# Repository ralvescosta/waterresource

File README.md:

# Water Resource

<br />
<br />

<p align="justify">
Water Resource é um projeto open source que tem como intuito apresentar para a comunidade de desenvolvimento um sistema de automação residencial utilizando o conceito de internet das coisas, integrando tecnologias modernas como: NodeJs, WebSocket, ReactJs, ESP32 dentre outras. O objetivo da aplicação é apresentar uma forma de monitorar e controlar o nível de um reservatório de água, juntamente com uma interface ao usuário, onde o usuário poderá acompanhar em tempo real o estado do sistema e interagir com o sensor configurando alguns parâmetros de aquisição. O sistema foi projetado para fornecer ao usuário confiabilidade e facilidade de controle. Leia mais sobre a aplicação em:
</p>

> https://waterresource.hopto.org

## Get Started

<p align="justify">
A seguir tem-se os passos para poder replicar os recursos do projeto, os itens Servidor-Local e Servidor-Remoto precisam ser hospedados em um ambiente virtual que tenha suporte para o mesmo, no minimo 1GB de memória RAM e 25GB de armazenamento. Cada tópico apresenta as medidas necessárias para poder colocar a aplicação em funcionamento tanto em um servidor local quanto em um servidor remoto.
</p>

- [Firmware](#Firmware)
  - [Premissas](##Premissas)
  - [Bibliotecas](##Bibliotecas)
  - [Upload-do-Firmware](##Embarcar-Firmware)
- [Servidor-Local](#Servidor-Local)
  - [Premissas](##Premissas)
  - [Back-End](##Back-End)
  - [Front-End](##Front-End)
- [Servidor-Remoto](#Servidor-Remoto)
  - [Premissas](##Premissas)
  - [Back-End](##Back-End)
  - [Front-End](##Front-End)
- [Hardware](#Hardware)
- [Referências](#Referências)
- [Licença](#Licença)

## Firmware

### Premissas

Inicialmente deve-se instalar o compilador utilizado:

- <a href="https://www.arduino.cc/en/Main/Software" target="_blank">Arduino IDE</a>

<p align="justify">
Com a IDE do Arduino devidamente instalada, instale as dependências da placa do ESP32 para que seja possível embarcar o firmewere no devKit ESP32, seguindo este <a href="https://www.fernandok.com/2018/09/instalando-esp32-no-arduino-ide-metodo.html" target="_blank">tutorial</a>.
</p>

<p align="justify">
Atente-se para o fato, que o projeto foi baseado na arquitetura do ESP32, sendo assim o funcionamento do mesmo só é garantido utilizando-o.
</p>

Após realizar devidamente as instalações clone o repositório:

> git clone https://github.com/rafaelbodao/waterresource.git

### Bibliotecas

<p align="justify">
Com a IDE devidamente configurada agora faz-se necessário instalar as bibliotecas que foram utilizadas no projeto. Por meio do gerenciador de bibliotecas da IDE, faça o download da biblioteca WiFi na versão 1.27 e ArduinoJson na versão 6.9.1. Ainda na instalação das bibliotecas porém agora instalando por meio de arquivos .zip, faça o download do seguintes repositórios com o formato .zip e insira-os na IDE <a href="https://github.com/zhouhan0126/WIFIMANAGER-ESP32" target="_blank">repositório 1</a>, <a href="https://github.com/zhouhan0126/DNSServer---esp32" target="_blank">repositório 2</a> e <a href="https://github.com/zhouhan0126/WebServer-esp32" target="_blank">repositório 3</a>
</p>

<p align="justify">
A biblioteca Web Service instalada por meio do repositório 3, possui um erro em sua arquitetura que faz gerar um conflito na renderização de um elemento HTML, assim faz-se necessário alterar o nome deste elemento no arquivo HTTP_Method.h. Para acessar este arquivo, só é possível por meio  do terminal. Com o Git Bash aberto deve-se acessar o diretório da biblioteca por meio do comando:
</p>

> cd c:\Users\YOUR_USER\AppData\Local\Arduino15\packages\esp32\hardware\esp32\1.0.0\libraries\WebService

<p align="justify">
Atente-se onde está escrito YOUR_USER deve-se inserir o usuário do computador onde foi instalado todas as dependências anteriormente. Ao acessar o devido diretório execute:
</p>

> sudo nano HTTP_Method.h

<p align="justify">
Acessando assim o conteúdo do arquivo. Encontre:
</p>

> HTTP_HEAD = 0b00100000

<p align="justify">
e substitua por:
</p>

> HTTP_HEADER = 0b00100000.

<p align="justify">
Após utilize o comando para fechar e salvar as alterações:
</p>

> Control + X

### Upload-do-Firmware
<p align="justify">
Com o repositório devidamente clonado, acesse o diretório firmware/WaterResource, abra e compile o arquivo WaterResource.ino. Após a compilação, faça o upload do firmware. A figura abaixo apresenta o esquemático a ser seguido para instalar os periféricos.
</p>

<p align="justify">
O protótipo desenvolvido com base no DevKit ESP32 e alguns outros periféricos tem como intuito ser uma plataforma de testes e não um produto para possível produção. O desenvolvimento de um hardware para a produção deve ser baseado no microcontrolador <a href="https://www.espressif.com/sites/default/files/documentation/esp32_datasheet_en.pdf" target="_blank">MCU ESP32</a> e não no DevKit ESP32, assim alem de reduzir consideravelmente o custo de cada sensor, o desepenho e a durabilidade do micocontrolador sera bem maior pois o mesmo tera apenas as funcionalidades necessarias para aplicação.
</p>

## Servidor-Local

### Premissas

Inicialmente instale os seguintes itens abaixo:

- <a href="https://nodejs.org/en/" target="_blank">NodeJs</a>
- <a href="https://gitforwindows.org/" target="_blank">Git Bash</a>
- <a href="https://www.apachefriends.org/pt_br/index.html" target="_blank">XAMPP</a>

Instale o gerenciador de processos <a href="http://pm2.keymetrics.io/" target="_blank">PM2</a>:

> sudo npm install pm2 -g

*Se estiver utilizando o Windows faz-se necessário executar o terminal como administrador

### Back-End

<p align="justify">
Com o repositório Water Resource clonado, e todos os passos anteriores realizados, acesse o diretório do repositório por meio do terminal, dentro da pasta backEnd execute o seguinte comando:
</p>

> npm install

<p align="justify">
Ao executá-lo será instalado todas as dependências necessárias. Na pasta backEnd, existe um arquivo denominado .env.exemple, porém este arquivo só pode ser visualizado por meio do terminal ou por algum editor de texto como por exemplo VSCode, ainda na pasta backEnd execute os comandos abaixo sequencialmente:
</p>

> cp .env.exemple .env

> sudo nano .env

<p align="justify">
Abrindo o conteúdo do arquivo, este arquivo contém as variáveis de ambiente que configuram toda a aplicação de back-end, caso você tenha seguido os passos anterior devidamente, simplesmente delete todo o conteúdo e copie o conteúdo logo abaixo e cole dentro do arquivo, caso tenha realizado os procedimentos anteriores de outra forma, entre com as devidas informações conforme é solicitado.
</p>

```javascript
module.exports = {
username: "root",
password: "",
database: "test",
host: "127.0.0.1",
dialect: "mysql",
saltRounds: 10,
tokenKey: "WR_2019_LOCAL_SERVER",
gmail:'YOUR_EMAIL_TO_SEND@gamil.com',
emailPassword: 'YOUR_EMAIL_PASSWORD',
}
```

<p align="justify">
Note que os campos gmail e emailPassword, deve ser inserido um e-mail e senha do gmail utilizado para enviar o email de confirmação de cadastro. Para que a aplicação de confirmação de cadastro por e-mail possa funcionar corretamente é necessário habilitar o acesso de aplicações de terceiros no gmail, faça o logIn no e-mail que deseja configurar e acesse este <a href="https://myaccount.google.com/lesssecureapps?utm_source=google-account&utm_medium=web" target="_blank">link</a>, habilitando assim o acesso a terceiros. Em seguida inicie o servidor Apache e o infraestrutura de banco de dados MySQL provida pelo XAMPP.
</p>

No diretório do backEnd digite o seguinte comando:

> node_modules\.bin\sequelize db:migrate

<p align="justify">
Ao executar este comando, se realizado os passos anteriores corretamente, será criado no banco de dados local a estrutura de persistência de dados, esta estrutura pode ser verificada acessando a aplicação de gerenciamento de banco de dados phpMyAdmin, digite em seu navegador de internet:
</p>

> localhost/phpmyadmin

<p align="justify">
Dentro da interface acesse o banco de dados test. A figura abaixo apresenta como é disposta a estrutura de dados.
</p>

<p align="justify">
O último passo é executar o servidor, para isso ainda dentro do diretório backEnd execute o seguinte comando:
</p>

> pm2 start src/server.js

<p align="justify">
Neste momento o servidor que cuidará de todas requisições provenientes do gateway (ESP 32) e da interface do usuário já está devidamente funcionando. Caso deseje verificar os status do servidor, basta digitar o seguinte comando:
</p>

> pm2 list

<p align="justify">
Caso queira parar o servidor, utilize o seguinte comando:
</p>

> pm2 stop src/server.js

### Front-End

<p align="justify">
Após realizar o procedimentos do Back-End em servidor local, abra uma nova aba do terminal e acesse o diretório frontEnd, execute o seguinte comando:
</p>

> npm install

<p align="justify">
Da mesma forma que foi realizado anteriormente, faz-se necessário modificar o arquivo de variáveis ambientes para configurar a aplicação, acesse o diretório frontEnd/src, por meio do comando:
<p>

> cd frontEnd/src

<p align="justify">
Altere o nome do arquivo “environment.exemple.js” para “environment.js”, utilizando o seguinte comando:
<p>

> mv environment.exemple.js environment.js

<p align="justify">
Se todos os passos foram seguidos corretamente, a única alteração necessária no arquivo será inserir o Ip local de onde a aplicação está sendo provida, assumindo o Ip local sendo: 192.168.100.3 a arquivo de configuração ficará:
<p>

```javascript
import socket from "socket.io-client"

/*
 * Dashboard exports
 */
export const dashboadURL = "http://192.168.100.3:3000";

export const socketIO = socket("http://192.168.100.3:3333");

export const difereceTime = 2;
/*
 * SignUp exports 
 */
export const hrefURL = "http://192.168.100.3:3000";

/*
 * Services exports
 */

//API AXIOS SERVICES
export const serverBaseURL = "http://192.168.100.3:3333";

//TOKEN ID
export const TOKEN_ID = "WR_IFMG"

```

<p align="justify">
Porém se foi realizado algum procedimento diferente, altere o arquivo environment.js conforme a necessidade. Por fim execute os comando abaixo em sequência:
</p>

> npm run build

> pm2 start server.js

<p align="justify">
Assim a aplicação Web estará pronta para uso em sua rede local, a mesma pode ser acessada por outros dispositivos que estiverem conectados a sua rede, basta acessar o Ip do computador que estiver hospedando a aplicação como por exemplo: 192.168.100.3:3000
</p>

<p align="justify">
Observação 1: Para que o serviço Web seja acessado é necessário realizar todos os procedimentos de inicialização, desde inicialização do XAMPP até a inicialização do Front-End.
</p>

<p align="justify">
Observação 2: O gateway está configurado para enviar as aquisições para o servidor local considerando um userId = 1, sendo assim faz necessário alterar o endereço do servidor local nas variáveis globais dentro do firmware e o Id do usuário criado no ato do cadastro do mesmo, considerando que o endereço Ip local do servidor seja 192.198.100.3 e o Id do usuario seja 1, a configuração das variáveis pode ser feita:
</p>

> \#define urlConfiguration “http://192.168.100.3:3333/gateway/configuration”

> \#define urlComunication “http://192.168.100.3:3333/gatewat/nivel”

> \#define userId 1

<!--  -->
## Servidor-Remoto

### Premissas

<p align="justify">
Para realizar o procedimento aqui apresentado faz-se necessário ter acesso a uma máquina virtual hospedada em alguma empresa de hospedagem. Utilizou-se uma máquina virtual hospedada no servidor da <a href="https://www.apachefriends.org/pt_br/index.html" target="_blank">Digital Ocean</a>, tendo 1GB de memória RAM, 25GB de armazenamento, com o sistema operacional Ubuntu 16.04.5 x64. Os procedimentos aqui apresentados funcionam especificamente para o sistema operacional utilizado.
</p>

<p align="justify">
Além da infraestrutura de hospedagem, faz-se necessário criar um “Sistema de nome de domínio” (DNS) para poder apontar para o Ip de sua máquina virtual, existem diversos provedores de DNS gratuitos, para a execução deste utilizou-se o <a href="https://www.apachefriends.org/pt_br/index.html" target="_blank">NO-IP</a>.
</p>

<p align="justify">
Após a criação do droplet Digital Ocean, será informado um acesso remoto a máquina virtual. Este acesso é criado de forma automática, com um usuário Root e uma senha. Existem boas práticas para poder configurar a conexão ssh com a máquina virtual, porém fica a cargo do leitor as realizá-las, neste iremos utilizar o acesso da forma em que é fornecido.
</p>

<p align="justify">
Antes de realizar o procedimento de hospedagem em um servidor remoto, realize o procedimento para servidor local, pois alguns passos realizados anteriormente serão fundamentais para esta etapa.
</p>

<p align="justify">
Abra o terminal de sua máquina local utilizando o Git Bash e digite os comandos sequencialmente:
</p>

> sudo apt-get updtae

> sudo apt-get install ssh

<p align="justify">
Tendo criado devidamente o droplet, o acesso a máquina virtual será realizado via conexão ssh por meio do IPv4 fornecido, considerando que o IPv4 fornecido seja “000:000:000:000”, execute o comando abaixo:
</p>

> ssh root@000:000:000:000

<p align="justify">
Em seguida será solicitado a senha de acesso, inserido a senha fornecida, você realizará o acesso remoto a seu ambiente de produção. Inicialmente faz-se necessário realizar a instalação de três dependências persistentes no pacote LEMP e configurá-las devidamente. A sigla LEMP representa as arquiteturas de desenvolvimento L = Linux, E = Enginex (nginx), M = MySQL e P = PHP, por meio destes pacotes podemos configurar toda a infraestrutura que vai receber a aplicação web.</p>

##### MySQL Server

<p align="justify">
A tecnologia MySQL é um ambeinte de desenvolvimento complexo e robusto, na sua versão 5.7 utiliza a base dados do MariaDB, execute o comando abaixo:
</p>

> sudo apt-get install mysql-server

<p align="justify">
Após a finalização da instalação do servidor MySQL, faz-se necessário configurá-lo, para isso digite o comando abaixo:
</p>

> mysql_secure_installation

<p align="justify">
Leia atentamente tudo que é informado e confira todas as solicitações que o MySQL irá dispor na tela. Após finalizar este procedimento verifique se a configuração foi realizada com sucesso, digitando o comando:
</p>

> systemctl status mysql.service

Caso o servidor estiver Off force a reinicialização:

> sudo systemctl start mysql

<p align="justify">
No momento em que foi instalado e configurado o servidor MySQL, gerou-se um usuário padrão, denominado root, assim faz-se necessário alterar a senha deste usuário para uma senha segura, criar uma base de dados e fornecer acesso do usuário a base de dados criada para a aplicação. Digite os comandos abaixo sequencialmente, atente-se onde está escrito 'password' insira sua senha.
</p>

> mysql -u root -p

> UPDATE mysql.user SET authentication_string = PASSWORD('password') WHERE User = 'root';

> FLUSH PRIVILEGES;

> CREATE DATABASE waterresource;

> GRANT ALL PRIVILEGES ON waterresource.* to root@localhost;

>FLUSH PRIVILEGES;

Digite o comando abaixo para verificar se a base de dados foi devidamente criada:

> SHOW DATABASE;

> exit

##### PHP-FPM
<p align="justify">
Com o banco de dados devidamente instalado e configurado, digite o comando abaixo, para instalar o processador de PHP:
</p>

>sudo apt-get install php-fpm php-mysql

>sudo nano /etc/php/7.0/fpm/php.ini

<p align="justify">
Busque pelo conteúdo:
</p>

> ;cgi.fix_pathinfo=1

e altere para:

> cgi.fix_pathinfo=0

Reinicie o processador PHP

>sudo systemctl restart php7.0-fpm

##### Nginx

<p align="justify">
Próximo passo é instalar o Nginx que fornecerá um servidor de conteúdo estático (utilizado na aplicação de gerenciamento do banco de dados phpMyAdmin) e gerenciamento do proxy reverso do servidor, execute o comando abaixo:
</p>

>sudo apt-get install nginx

>sudo ufw allow 'Nginx HTTP'

<p align="justify">
Habilite o FireWall para aceitar solicitações do tipo HTTP e HTTPS, executando os comandos abaixo em sequência.
</p>

>sudo ufw allow OpenSSH

>sudo ufw allow http

>sudo ufw allow https

>sudo ufw enable

<p align="justify">
Neste momento se todos os procedimentos foram realizados corretamente, é possível acessar o IPv4 da máquina virtual, sendo renderizado a página de boas vindas do Nginx.
</p>

##### NodeJs

<p align="justify">
Instale o NodeJs por meio do repositório do Node, execute os comandos abaixo de forma sequencial.
</p>

>sudo apt-get install curl

>curl -sL https://deb.nodesource.com/setup_10.x | sudo bash -

>sudo apt install nodejs

Instale o gerenciador de processos <a href="http://pm2.keymetrics.io/" target="_blank">PM2</a>:

>sudo npm install pm2 -g

##### Let's Encrypt

<p align="justify">
O próximo passo é configurar o certificado SSL de criptografia, existem diversas formas de obter esta certificação, uma delas é utilizando o Let’s Encrypt que é uma aplicação criada e sustentada pela Linux Foundation, permitindo estabelecer conexões seguras de forma simples e gratuita. Execute os comandos abaixo de forma sequencial.
</p>

>sudo apt-get install bc

>sudo git clone https://github.com/letsencrypt/letsencrypt /opt/letsencrypt

<p align="justify">
Para criar a certificação é necessário ter criado um DNS previamente, assumindo que o DNS criado chama-se meusite.com.br. Execute os comandos de forma sequencial.
</p>

>dig +short meusite.com.br

Retornando o IPv4 para onde o DNS aponta.

>cd /opt/letsencrypt

>./certbot-auto certonly --standalone

>/opt/letsencrypt/certbot-auto renew

<p align="justify">
Ao realizar esta etapa, o certificado estará devidamente configurado e renovará sua chave de segurança de forma automática mensalmente.
</p>

<p align="justify">
Para garatir a segurança criptografia configurada, faz necessario utilizar uma tecnologia de trocas de chave, optou-se por utilizar o DIFFIE-HELLMAN GROUP. Assim para configurar corretamente a certificação, execute os comandos abaixo:
</p>

> sudo openssl dhparam -out /etc/ssl/certs/dhparam.pem 2048

O comando acima executa um procedimento que pode levar alguns minutos.

> sudo nano /etc/nginx/snippets/ssl-params.conf

Dentro do arquivo de configuração criado, insira:
```
ssl_protocols TLSv1 TLSv1.1 TLSv1.2;
ssl_prefer_server_ciphers on;
ssl_ciphers "EECDH+AESGCM:EDH+AESGCM:AES256+EECDH:AES256+EDH";
ssl_ecdh_curve secp384r1; # Requires nginx >= 1.1.0
ssl_session_cache shared:SSL:10m;
ssl_session_tickets off; # Requires nginx >= 1.5.9
ssl_stapling on; # Requires nginx >= 1.3.7
ssl_stapling_verify on; # Requires nginx => 1.3.7
resolver 8.8.8.8 8.8.4.4 valid=300s;
resolver_timeout 5s;
add_header Strict-Transport-Security "max-age=63072000; includeSubDomains; preload";
add_header X-Frame-Options DENY;
add_header X-Content-Type-Options nosniff;

# Add our strong Diffie-Hellman group
ssl_dhparam /etc/ssl/certs/dhparam.pem;
```
Execute o comando para sair do arquivo e salvar as alterações:

> Control + X

##### Proxy Reverso

<p align="justify">
Por definição do protocolo HTTP ao acessarmos um servidor por meio de seu IPv4, a requisição é direcionada diretamente para a aplicação da porta 80, sendo assim ao acessar o domínio que aponta para o IPv4 diretamente o acesso é direcionado para a porta 80, para direcionar o acesso do DNS para as devidas aplicações faz-se necessário redirecionar todas as requisições que chegam direto ao IPv4 da aplicação para as aplicações na porta 3000 (onde é provido o front-end) e 3333 (onde é provido a back-end). Execute o comando abaixo</p>

> sudo nano /etc/nginx/sites-enabled/default

Dentro do arquivo, apague todo o conteúdo e copie o conteúdo apresentado abaixo. Atente-se onde está escrito 'meusite.com.br', insira o seu DNS.
```
# HTTPS  proxy all requests to the Node app
server {
# Enable HTTP/2
listen 443 ssl http2;
listen [::]:443 ssl http2;

server_name meusite.com.br;

root /var/www/html;
index index.php index.html index.htm index.nginx-debian.html;

# Use the Lets Encrypt certificates
ssl_certificate /etc/letsencrypt/live/meusite.com.br/fullchain.pem;
ssl_certificate_key /etc/letsencrypt/live/meusite.com.br/privkey.pem;

# Include the SSL configuration from cipherli.st
include snippets/ssl-params.conf;

   location /phpmyadmin {
          root /usr/share/;
          index index.php index.html index.htm;
          location ~ ^/phpmyadmin/(.+\.php)$ {
                  try_files $uri =404;
                  root /usr/share/;
                  fastcgi_pass 127.0.0.1:9000;
                  fastcgi_index index.php;
                  fastcgi_param SCRIPT_FILENAME $document_root$fastcgi_script_name;
                  include /etc/nginx/fastcgi_params;
          }
          location ~* ^/phpmyadmin/(.+\.(jpg|jpeg|gif|css|png|js|ico|html|xml|txt))$ {
                  root /usr/share/;
          }
   }
   location /phpMyAdmin {
          rewrite ^/* /phpmyadmin last;
   }
    location ~ \.php$ {
       include snippets/fastcgi-php.conf;
       fastcgi_pass unix:/run/php/php7.0-fpm.sock;
   }

   location ~ /\.ht {
       deny all;
   }
    location / {
       proxy_set_header X-Real-IP $remote_addr;
       proxy_set_header X-Forwarded-For $proxy_add_x_forwarded_for;
       proxy_set_header X-NginX-Proxy true;
       proxy_pass http://localhost:3000/;
       proxy_ssl_session_reuse off;
       proxy_set_header Host $http_host;
       proxy_cache_bypass $http_upgrade;
       proxy_redirect off;
   }
    location /backend {
       proxy_set_header X-Real-IP $remote_addr;
       proxy_set_header X-Forwarded-For $proxy_add_x_forwarded_for;
       proxy_set_header X-NginX-Proxy true;
       proxy_pass http://localhost:3333/socket.io/;
       proxy_ssl_session_reuse off;
       proxy_set_header Host $http_host;
       proxy_cache_bypass $http_upgrade;
       proxy_redirect off;
   }

   location /backend/users {
       proxy_set_header X-Real-IP $remote_addr;
       proxy_set_header X-Forwarded-For $proxy_add_x_forwarded_for;
       proxy_set_header X-NginX-Proxy true;
       proxy_pass http://localhost:3333/users/;
       proxy_ssl_session_reuse off;
       proxy_set_header Host $http_host;
       proxy_cache_bypass $http_upgrade;
       proxy_redirect off;
   }
   location /backend/gateway {
       proxy_set_header X-Real-IP $remote_addr;
       proxy_set_header X-Forwarded-For $proxy_add_x_forwarded_for;
       proxy_set_header X-NginX-Proxy true;
       proxy_pass http://localhost:3333/gateway/;
       proxy_ssl_session_reuse off;
       proxy_set_header Host $http_host;
       proxy_cache_bypass $http_upgrade;
       proxy_redirect off;
   }
}

```
Em seguida reinicie o restart o Nginx:

> sudo systemctl start nginx

> sudo systemctl restart nginx

Verifique se o procedimento foi realizado corretamente por meio do comando:

>s udo nginx -t

<p align="justify">
Assim o Nginx retorna o status da configuração, caso retorne algum possível erro, refaça todo o procedimento de configuração do Nginx.
</p>

##### phpMyAdmin
<p align="justify">
Phpmyadmin é uma aplicação de fácil utilização para gerenciamento de banco de dados relacionais, execute o comando abaixo:
</p>

> sudo apt-get install phpmyadmin

<p align="justify">
Durante a instalação será requisitado algumas configurações. Primeiramente solicita-se a configuração do servidor que suportará a aplicação, o gerenciador de instalação irá apresentar duas tecnologias apache2 e lighttpd, como não será utilizado nenhuma das duas, apenas pressione TAB e em seguida ENTER. O gerenciador de instalação questionará se deseja configurar a aplicação do phpmyadmin por meio do dbconfig-commun, selecione NAO para dar prosseguimento a instalação. O acesso a aplicação de gerenciamento de banco de dados necessita de uma configuração de segurança, para que somente usuários credenciados possa acessar a rota da aplicação, execute o comando abaixo:
</p>

> sudo apt install apache2-utils

<p align="justify">
Em seguida configure um usuário e senha, ao executar o comando abaixo cria-se um usuário com o nome ‘myuser’ e uma senha relacionada a este usuário.
</p>

> sudo htpasswd -c /etc/nginx/.htpasswd myuser

Reinicie o Nginx:
> sudo systemctl start nginx

> sudo systemctl restart nginx

<p align="justify">
Assim so é possivel acessar a rota ‘meusite.com.br/phpmyadmin’ inserindo as credenciais criadas anteriormente.
</p>

<p align="justify">
Tendo realizado devidamente todo o procedimento apresentado, pode-se iniciar o processo de deploy da aplicação. Inicialmente deve-se criar um repositório PRIVADO com seu acesso ao Github, pois o ambiente de produção dificulta realizar algumas alterações no aplicação, sendo assim antes de enviar a aplicação para a máquina virtual, iremos alterá-la para que não haja necessidade fazer essas alterações via terminal. 
</p>
<p align="justify">
Tendo criado o repositório PRIVADO para deploy, clone este repositório em um diretório em seu computador. Após clonar copie e cole neste diretório as pastas frontEnd e backEnd, assim a partir de agora sempre que referenciar backEnd ou frontEnd estará sendo referindo ao repositório de deploy
</p>

<p align="justify">
No diretório do backEnd, deve-se alterar o arquivo de variáveis ambientais para as configurações realizadas na máquina virtual, como mostrado o exemplo abaixo:
</p>

```javascript
module.exports = {
  username: "root",
  password: "YOUR_ROOT_PASSWORD",
  database: "waterresource",
  host: "127.0.0.1",
  dialect: "mysql",

  saltRounds: 10,
  
  tokenKey: "WTR_2019",

  gmail:'YOUR_EMAIL@gmail.com',
  emailPassword: YOUR_EMAIL_PASSWORD,

  emailURL: "https://MEUSITE.COM.BR/emailconfirme?rock={1}"
}

```
<p align="justify">
Salve as alterações e em seguida exclua o arquivo .gitignore que esta no diretorio do backEnd, executando o comando abaixo:
</p>

> sudo rm -rf .gitignore

<p align="justify">
Acesse o diretório do frontEnd, exclua o arquivo .gitignore, semelhante ao que foi feito anteriormente, abra o arquivo src/environment.js, apague todo o conteúdo e copie o conteúdo apresentado abaixo:
</p>

```javascript
import socket from "socket.io-client"

/*
* Dashboard exports
*/
export const dashboadURL = "https://MEUSITE.COM.BR";

export const socketIO = socket.connect('https://MEUSITE.COM.BR', {path: '/backend'});

export const difereceTime = 2;
/*
* SignUp exports
*/
export const hrefURL = "https://MEUSITE.COM.BR";

/*
* Services exports
*/

//API AXIOS SERVICES
export const serverBaseURL = "https://MEUSITE.COM.BR/backend";

//TOKEN ID
export const TOKEN_ID = "WTR_2019"
```
<p align="justify">
Atente-se para onde está indicado ‘MEUSITE.COM.BR’, deve ser inserido o DNS configurado anteriormente. Salve o arquivo e execute o comando abaixo:
</p>

> npm run build

<p align="justify">
Em seguida faça o commit e o push para o seu repositório de deploy.
</p>

### Back-End
<p align="justify">
Com o acesso a máquina virtual, execute os comandos abaixo em sequência:
</p>

> cd

> mdkdir WaterResourcer

> cd WaterResourcer

<p align="justify">
Clone o repositório, executando o comando abaixo: 
</p>

>git clone https://github.com/YOURGITHUB/deploy.git

<p align="justify">
Sendo um repositório privado, será preciso inserir suas credenciais do Github para realizar o procedimento de clonagem. Em seguida acesse o diretório do backEnd, executando o comando abaixo:
</p>

> cd 

> cd WaterResourcer/deploy/backEnd

<p align="justify">
Instale as dependências da aplicação, utilizando o comando abaixo:
</p>

> npm install

<p align="justify">
Crie a arquitetura de persistência de dados da aplicação, execute o comando abaixo:
</p>

> node_modules/.bin/sequelize db:migrate

<p align="justify">
Acessando a aplicação de gerenciamento do banco de dados phpMyAdmin é possível constatar se foi criado de fato a arquitetura de persistência de dados.
</p>

<p align="justify">
Inicialize o Back-End utilizando o comando abaixo:
</p>

>pm2 start src/server.js

### Front-End
<p align="justify">
Acesse o diretório do frontEnd, executando os comandos abaixo:
</p>

> cd

> cd WaterResourcer/deploy/frontEnd

<p align="justify">
Instale as dependências executando o comando:
</p>

>npm install

<p align="justify">
Por fim coloque a aplicação de Front-End no ar executando o comando abaixo:
</p>

>pm2 start server.js

<p align="justify">
Qualquer duvidas entre em contato por meio do email: rafael.rac.mg@gmail.com
</p>

## Referências

##### Firmware

<a href="https://www.espressif.com/en/products/hardware/esp32/overview" target="_blank">ESP 32</a><br />
<a href="https://github.com/tzapu/WiFiManager" target="_blank">Wifi Manager</a><br />
<a href="https://www.arduino.cc/reference/en/" target="_blank">Arduino IDE</a><br />

##### Infraestrutura

<a href="https://www.digitalocean.com/" target="_blank">Digital Ocean</a><br />
<a href="https://www.nginx.com/" target="_blank">Nginx</a><br />
<a href="https://www.mysql.com/" target="_blank">MySQL</a><br />
<a href="https://letsencrypt.org/" target="_blank">Let's Encrypt</a><br />
<a href="https://www.phpmyadmin.net/" target="_blank">phpMyAdmin</a><br />
<a href="https://code.lengstorf.com/deploy-nodejs-ssl-digitalocean/" target="_blank">Deploying Aplications in Digital Ocean - Jason Lengstrof</a><br />

##### Back-End

<a href="https://nodejs.org/en/" target="_blank">NodeJs</a><br />
<a href="https://expressjs.com/pt-br/" target="_blank">ExpressJs</a><br />
<a href="https://github.com/expressjs/cors" target="_blank">Cors</a><br />
<a href="https://socket.io/" target="_blank">Socket.io</a><br />
<a href="https://www.npmjs.com/package/bcryptjs" target="_blank">bcryptJs</a><br />
<a href="https://jwt.io/" target="_blank">JWT</a><br />
<a href="http://docs.sequelizejs.com/" target="_blank">Sequelize</a><br />
<a href="https://nodemailer.com/about/" target="_blank">Nodemailer</a><br />

##### Front-End

<a href="https://reactjs.org/" target="_blank">ReactJs</a><br />
<a href="https://reactstrap.github.io/" target="_blank">React Bootstrap</a><br />
<a href="https://fontawesome.com/" target="_blank">React Font Awesome</a><br />
<a href="https://pushjs.org/" target="_blank">Push Notification</a><br />
<a href="https://socket.io/docs/client-api/" target="_blank">Socket.io-client</a><br />
<a href="https://github.com/axios/axios" target="_blank">Axios</a><br />

## Licença

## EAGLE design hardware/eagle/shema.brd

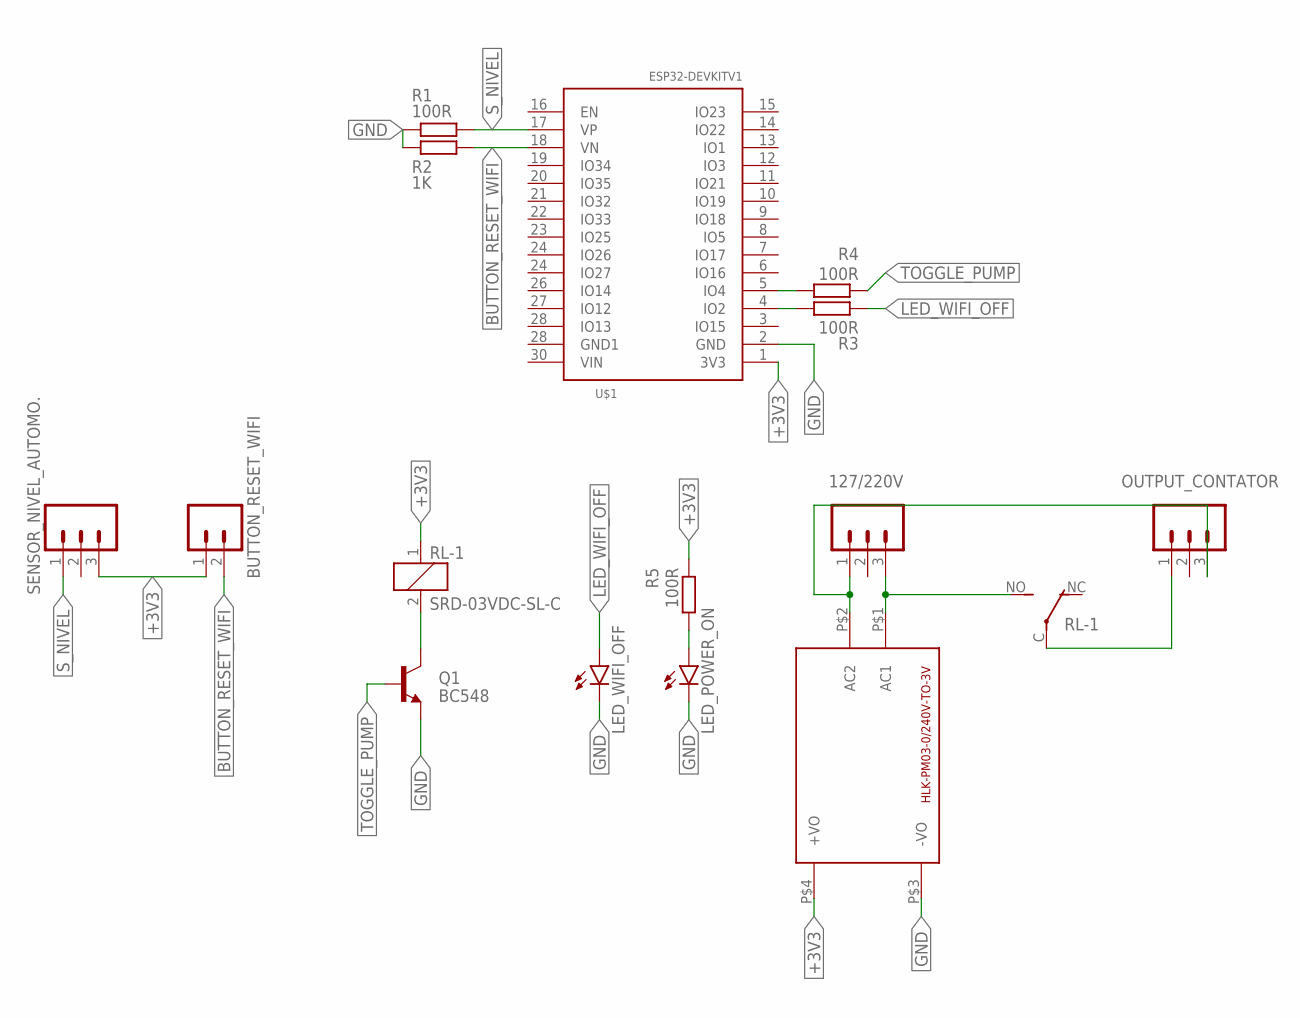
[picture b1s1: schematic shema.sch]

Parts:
127/220V: M03; 03P
BUTTON_RESET_WIFI: M02; 02P
HLK-PM03-0/240V-TO-3V: HLK-PM013W; HLK-PM01
LED_POWER_ON: LED3MM
LED_WIFI_OFF: LED3MM
OUTPUT_CONTATOR: M03; 03P
Q1: BC548; TO92-EBC
R1, R3, R4, R5: 100R; 0207/10
R2: 1K; 0207/10
RL-1: SRD-03VDC-SL-C; CQ1
SENSOR_NIVEL_AUTOMO.: M03; 03P
U$1: ESP32DEVKITV1; ESP32-DEVKITV1

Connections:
+3V3: BUTTON_RESET_WIFI.1, HLK-PM03-0/240V-TO-3V.P$4 (+VO), R5.1, RL-1.1, SENSOR_NIVEL_AUTOMO..3, U$1.1 (3V3)
BUTTON_RESET_WIFI: BUTTON_RESET_WIFI.2, R2.2, U$1.18 (VN)
GND: HLK-PM03-0/240V-TO-3V.P$3 (-VO), LED_POWER_ON.K (C), LED_WIFI_OFF.K (C), Q1.E, R1.1, R2.1, U$1.2 (GND)
LED_WIFI_OFF: LED_WIFI_OFF.A, R3.1
unnamed: R3.2, U$1.4 (IO2)
unnamed: 127/220V.3, HLK-PM03-0/240V-TO-3V.P$1 (AC1), RL-1.NO (S)
unnamed: R4.2, U$1.5 (IO4)
unnamed: Q1.C, RL-1.2
unnamed: OUTPUT_CONTATOR.1, RL-1.C
unnamed: 127/220V.1, HLK-PM03-0/240V-TO-3V.P$2 (AC2), OUTPUT_CONTATOR.3
unnamed: LED_POWER_ON.A, R5.2
S_NIVEL: R1.2, SENSOR_NIVEL_AUTOMO..1, U$1.17 (VP)
TOGGLE_PUMP: Q1.B, R4.1

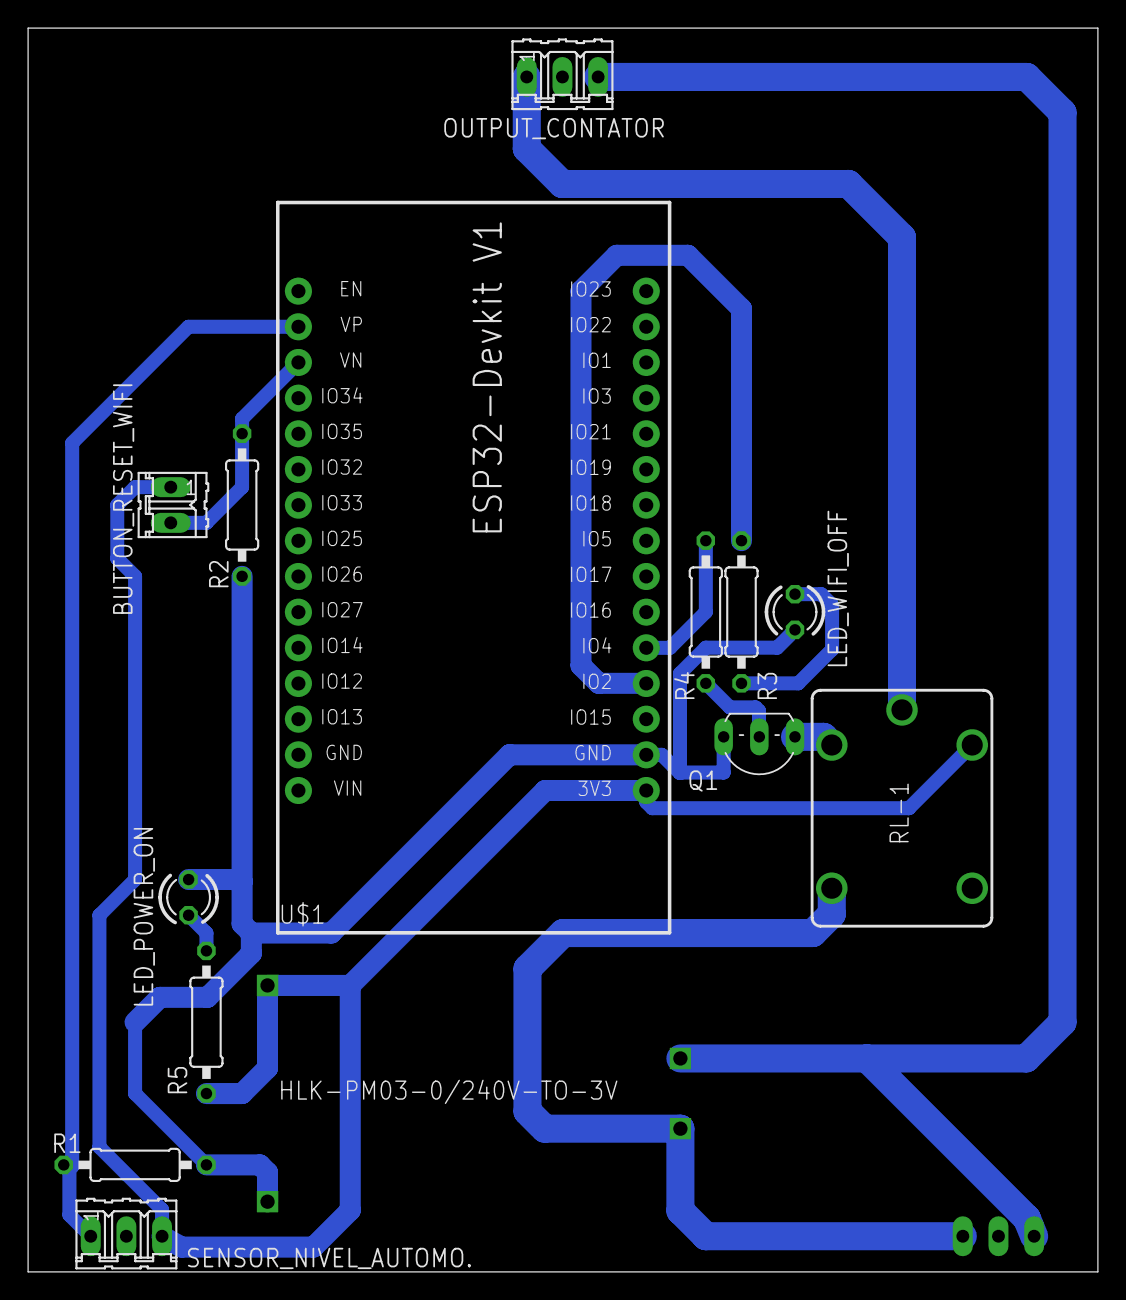
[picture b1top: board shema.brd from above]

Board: 2 copper layers, 76.2 x 88.6 mm, 15 parts (1 on the bottom side), 13 nets.

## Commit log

2019-03-18 This is an open source project developed in partnership with the IFMG campus Formiga / MG in the development of the course completion work
2019-03-18 change in readme.md
2019-03-19 send resumo in article
2019-03-21 change the websocket gatwey filter
2019-03-22 hardware
2019-03-23 alterações na dashboard - Inserido Bodas Vindas e amotra do tempo da ultima aquisição
2019-05-25 Monografia
